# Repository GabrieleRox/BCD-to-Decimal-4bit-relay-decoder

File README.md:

# BCD-to-Decimal 4bit relay decoder

This board was born from my passion for retrocomputers and electronics, as an electromechanical reinterpretation of a modern circuit with the aim of creating a set of simple logic operators schemes. Initially conceived as a component of an electromechanical clock, it can be adapted to any type of application, thanks to a simple design that is easy to adapt to different operating conditions.

The scheme of this board was inspired by the logic scheme of an IC of the 4000 family, converting the logic gates into electromechanical logic. The scheme obtained was then optimized trying to exploit all the available contacts of the relays, in order to create a compact board and as simple as possible and with few connections.

## Features

There are 28 HRS1H-S-DC12V signal relays on the board. These are 12V 6-pin relays, each of which can support up to 1A of current and consume just 200mW. The use of these relays allows to adapt the board to operate at different voltages, by appropriately choosing the operating voltage of the relays. The output is designed for the direct driving of a 7-segment display with common anode, which can be powered in this way even at a voltage different from that of the board. 4 LEDs have also been included to display the input binary code.

Finally, a set of serigraphs guides the user in fixing and connecting.

## Technical specifications

- Power supply voltage: 12V
- Current per channel: max 1.8A
- Current supported for each segment: max 1A
- Board size: 100 x 83.5 mm
- Dimension for fixing: 93 x 75 mm

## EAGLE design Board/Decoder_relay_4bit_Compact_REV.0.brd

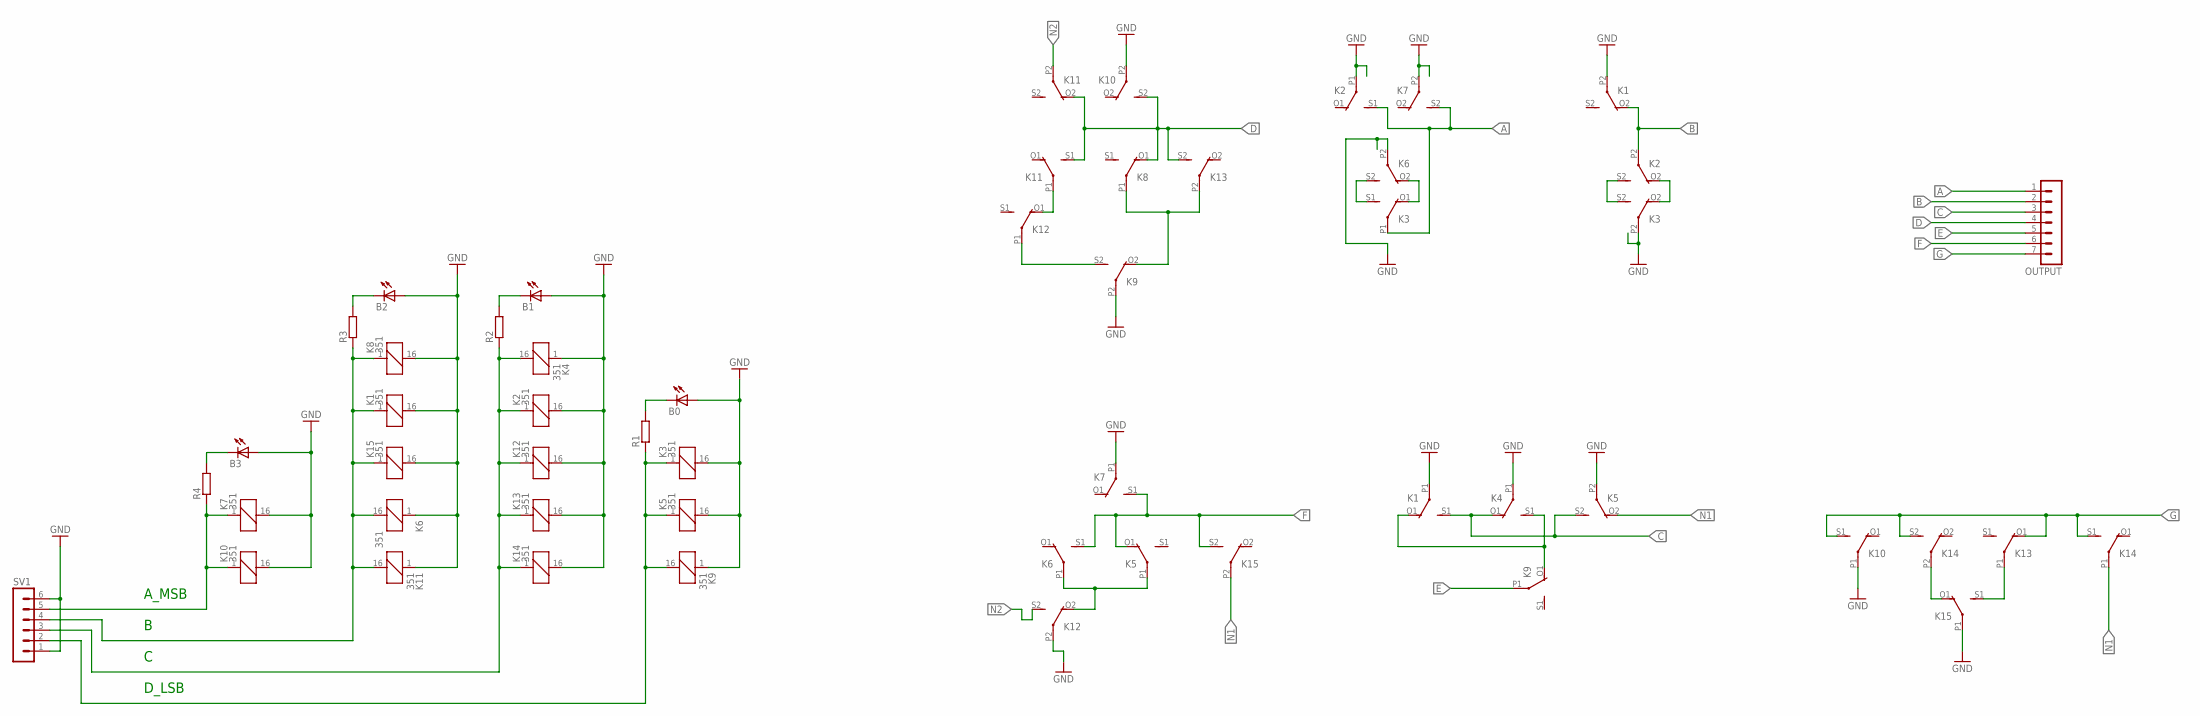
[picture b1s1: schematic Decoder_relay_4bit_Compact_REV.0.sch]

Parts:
B0, B1, B2, B3: LED3MM
K1, K2, K3, K4, K5, K6, K7, K8, K9, K10, K11, K12, K13, K14, K15: 351
OUTPUT: MA07-1
R1, R2, R3, R4: R-EU_M0805; M0805
SV1: MA06-1

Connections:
A: K2.S1 (S), K3.P1, K7.S2 (S), OUTPUT.1
A3: K7.1, K10.1, R4.1, SV1.5
B: K1.O2 (O), K2.P2, OUTPUT.2
C: K1.S1 (S), K4.O1 (O), K5.S2 (S), OUTPUT.3
D: K8.O1 (O), K10.S2 (S), K11.O2 (O), K11.S1 (S), K13.S2 (S), OUTPUT.4
E: K9.P1, OUTPUT.5
F: K5.O1 (O), K6.S1 (S), K7.S1 (S), K15.S2 (S), OUTPUT.6
G: K10.S1 (S), K13.O1 (O), K14.S1 (S), K14.S2 (S), OUTPUT.7
GND: B0.A, B1.A, B2.A, B3.A, K1.16 (2), K1.P1, K1.P2, K2.16 (2), K2.P1, K3.16 (2), K3.P2, K4.1, K4.P1, K5.16 (2), K5.P2, K6.1, K6.P2, K7.16 (2), K7.P1, K7.P2, K8.16 (2), K9.1, K9.P2, K10.16 (2), K10.P1, K10.P2, K11.1, K12.16 (2), K12.P2, K13.16 (2), K14.16 (2), K15.16 (2), K15.P1, SV1.1, SV1.6
N1: K5.O2 (O), K14.P1, K15.P2
N2: K11.P2, K12.S2 (S)
unnamed: K8.P1, K9.O2 (O), K13.P2
unnamed: B0.K (C), R1.2
unnamed: K2.S2 (S), K3.S2 (S)
unnamed: B1.K (C), R2.2
unnamed: K3.S1 (S), K6.S2 (S)
unnamed: B2.K (C), R3.2
unnamed: B3.K (C), R4.2
unnamed: K5.P1, K6.P1, K12.O2 (O)
unnamed: K2.O2 (O), K3.O2 (O)
unnamed: K13.P1, K15.S1 (S)
unnamed: K14.P2, K15.O1 (O)
unnamed: K9.S2 (S), K12.P1
unnamed: K11.P1, K12.O1 (O)
unnamed: K3.O1 (O), K6.O2 (O)
unnamed: K1.O1 (O), K4.S1 (S), K9.O1 (O)
unnamed: K1.1, K6.16 (2), K8.1, K11.16 (2), K15.1, R3.1, SV1.4
unnamed: K3.1, K5.1, K9.16 (2), R1.1, SV1.2
unnamed: K2.1, K4.16 (2), K12.1, K13.1, K14.1, R2.1, SV1.3

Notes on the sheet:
A_MSB
D_LSB

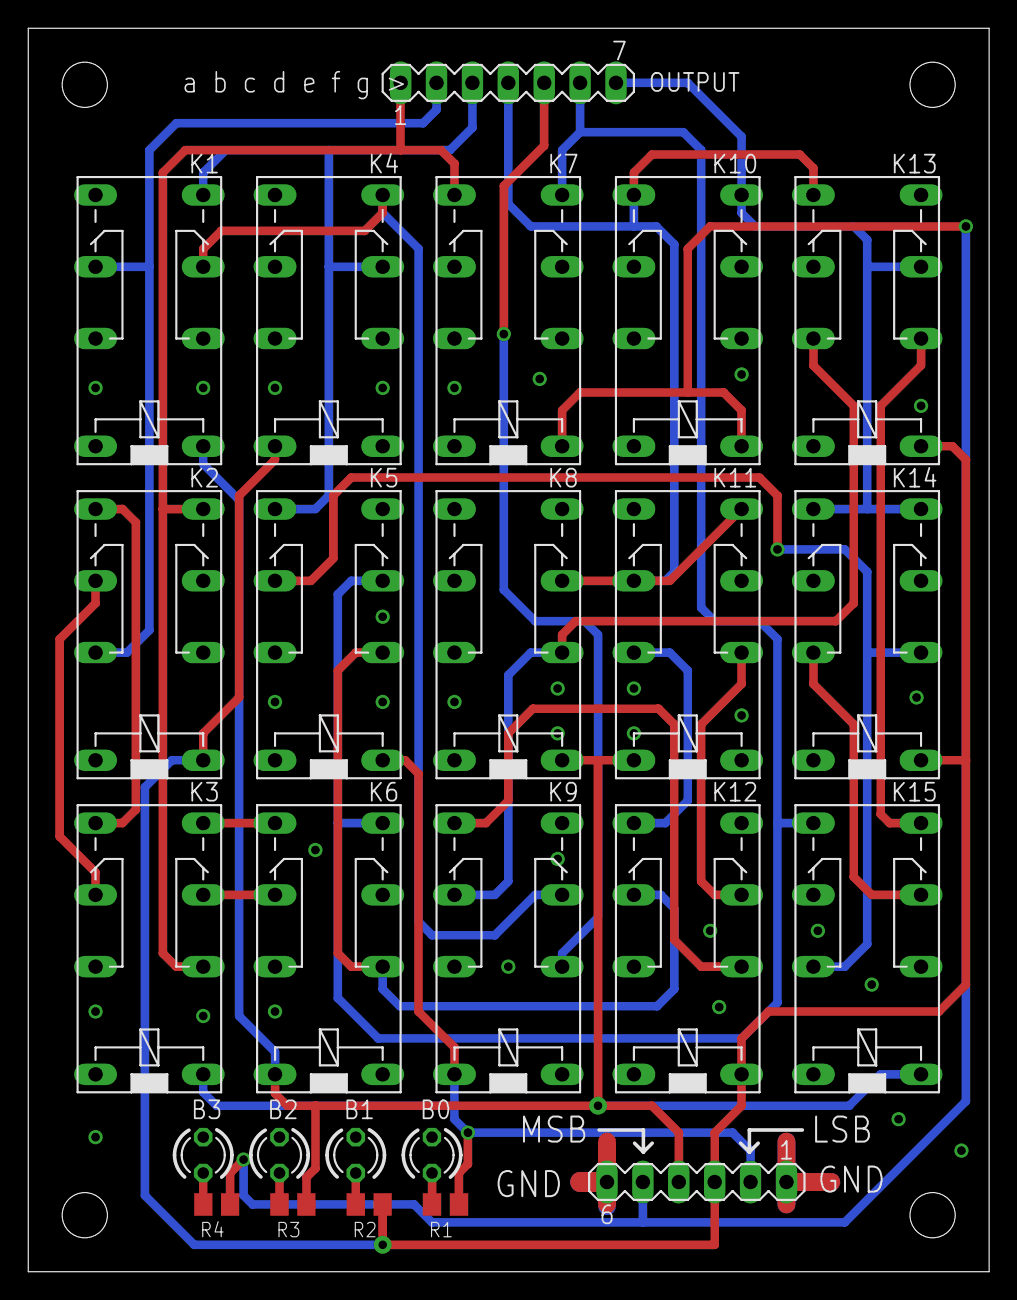
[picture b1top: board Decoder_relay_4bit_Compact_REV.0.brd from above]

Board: 2 copper layers, 68.0 x 88.0 mm, 25 parts (0 on the bottom side), 29 nets.

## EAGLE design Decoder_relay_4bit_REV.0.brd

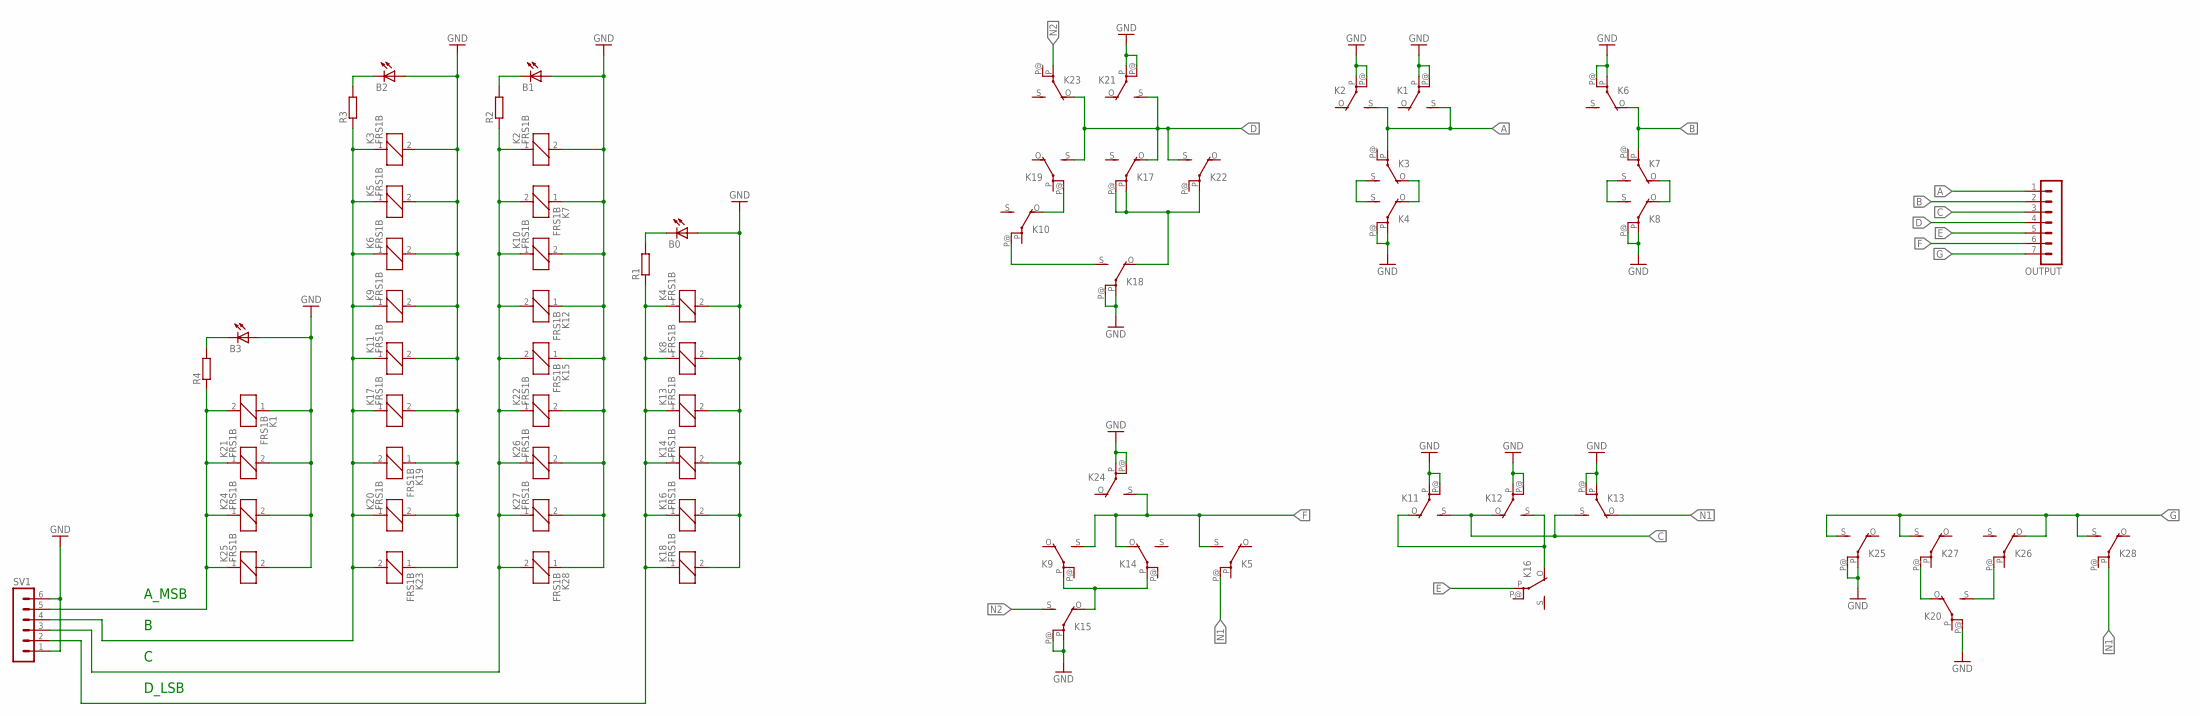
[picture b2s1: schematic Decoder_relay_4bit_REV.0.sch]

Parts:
B0, B1, B2, B3: LED3MM
K1, K2, K3, K4, K5, K6, K7, K8, K9, K10, K11, K12, K13, K14, K15, K16, K17, K18, K19, K20, K21, K22, K23, K24, K25, K26, K27, K28: FRS1B
OUTPUT: MA07-1
R1, R2, R3, R4: R-EU_M1206; M1206
SV1: MA06-1

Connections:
A: K1.S, K2.S, K3.P, OUTPUT.1
A3: K1.2, K21.1, K24.1, K25.1, R4.1, SV1.5
B: K6.O, K7.P, OUTPUT.2
C: K11.S, K12.O, K13.S, OUTPUT.3
D: K17.O, K19.S, K21.S, K22.S, K23.O, OUTPUT.4
E: K16.P, OUTPUT.5
F: K5.S, K9.S, K14.O, K24.S, OUTPUT.6
G: K25.S, K26.O, K27.S, K28.S, OUTPUT.7
GND: B0.A, B1.A, B2.A, B3.A, K1.1, K1.P, K1.P@, K2.2, K2.P, K2.P@, K3.2, K4.2, K4.P, K4.P@, K5.2, K6.2, K6.P, K6.P@, K7.1, K8.2, K8.P, K8.P@, K9.2, K10.2, K11.2, K11.P, K11.P@, K12.1, K12.P, K12.P@, K13.2, K13.P, K13.P@, K14.2, K15.1, K15.P, K15.P@, K16.2, K17.2, K18.2, K18.P, K18.P@, K19.1, K20.2, K20.P@, K21.2, K21.P, K21.P@, K22.2, K23.1, K24.2, K24.P, K24.P@, K25.2, K25.P, K25.P@, K26.2, K27.2, K28.1, SV1.1, SV1.6
N1: K5.P@, K13.O, K28.P
N2: K15.S, K23.P
unnamed: K17.P, K17.P@, K18.O, K22.P
unnamed: B0.K (C), R1.2
unnamed: K7.S, K8.S
unnamed: B1.K (C), R2.2
unnamed: K3.S, K4.S
unnamed: B2.K (C), R3.2
unnamed: B3.K (C), R4.2
unnamed: K9.P, K14.P, K15.O
unnamed: K7.O, K8.O
unnamed: K20.S, K26.P@
unnamed: K20.O, K27.P@
unnamed: K10.P@, K18.S
unnamed: K10.O, K19.P@
unnamed: K3.O, K4.O
unnamed: K11.O, K12.S, K16.O
unnamed: K3.1, K5.1, K6.1, K9.1, K11.1, K17.1, K19.2, K20.1, K23.2, R3.1, SV1.4
unnamed: K4.1, K8.1, K13.1, K14.1, K16.1, K18.1, R1.1, SV1.2
unnamed: K2.1, K7.2, K10.1, K12.2, K15.2, K22.1, K26.1, K27.1, K28.2, R2.1, SV1.3

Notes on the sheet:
A_MSB
D_LSB

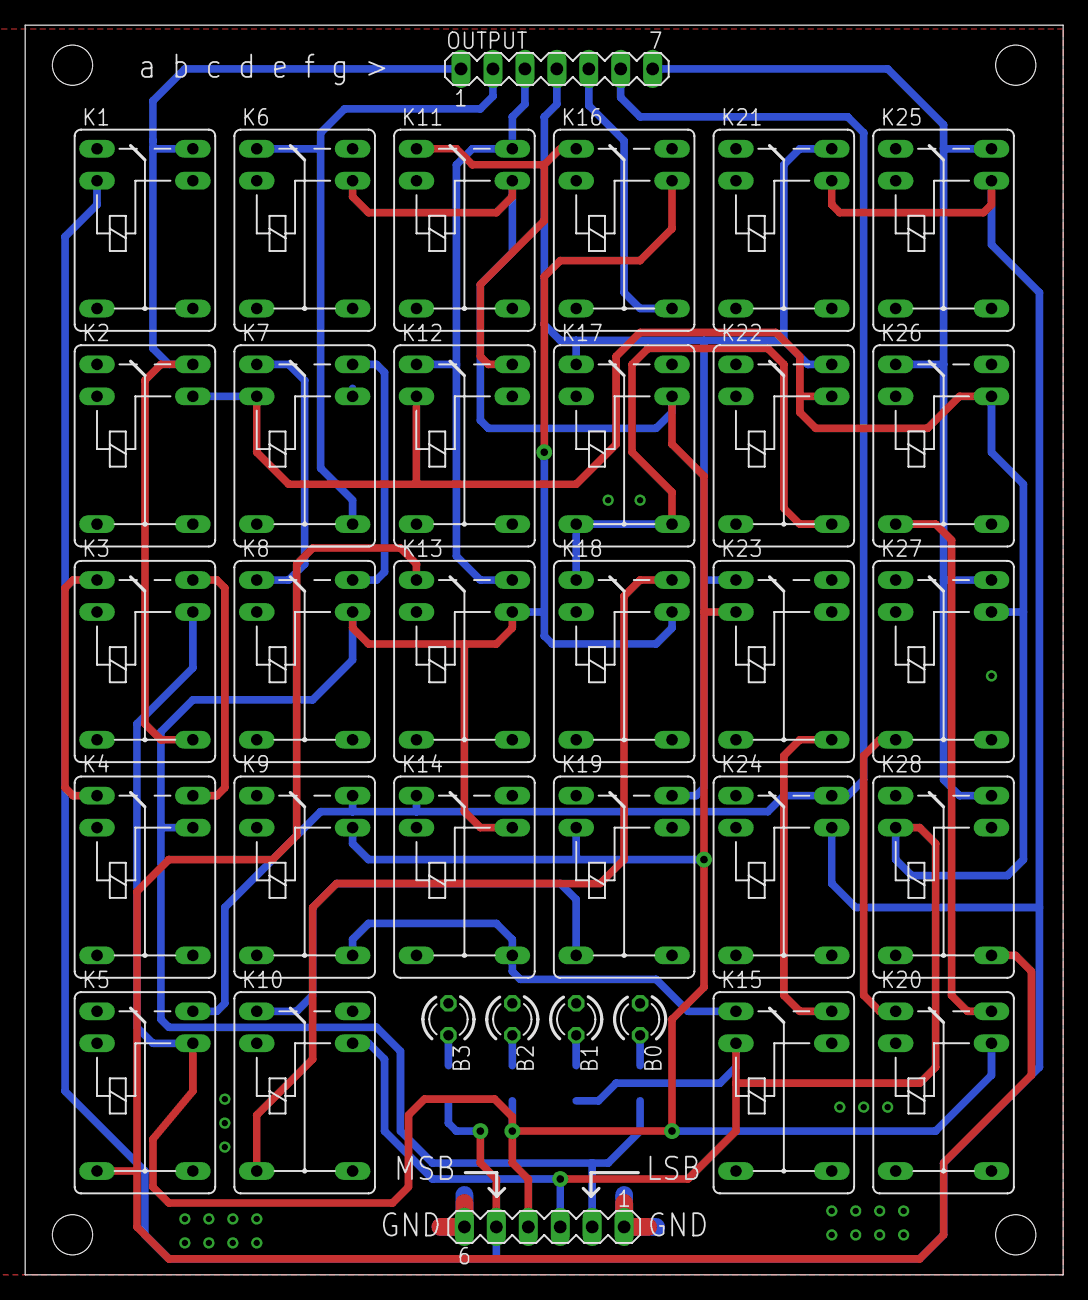
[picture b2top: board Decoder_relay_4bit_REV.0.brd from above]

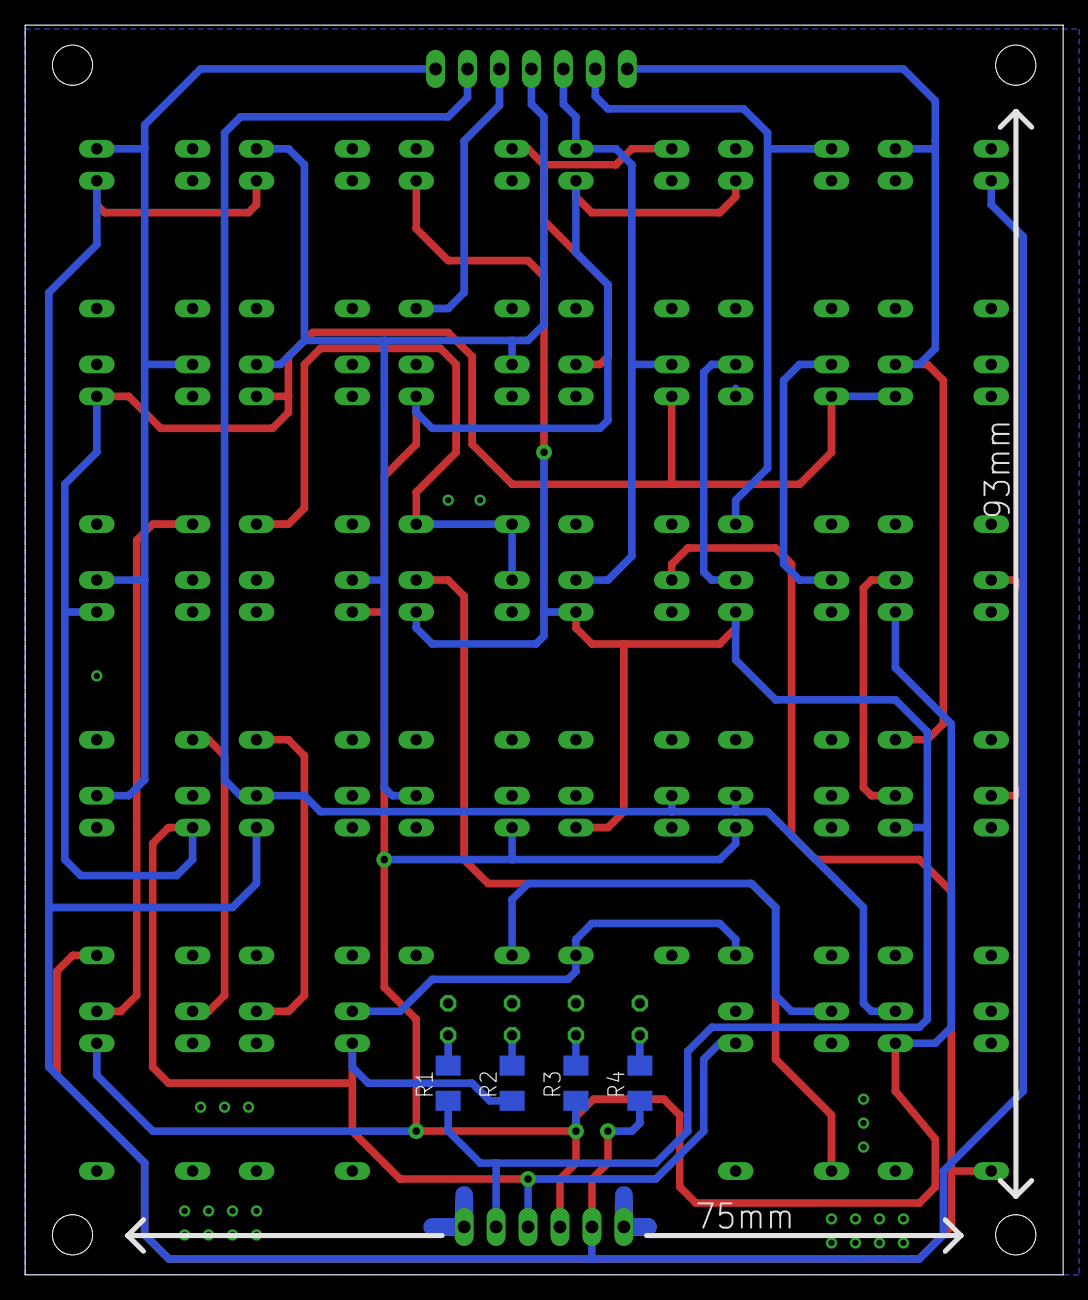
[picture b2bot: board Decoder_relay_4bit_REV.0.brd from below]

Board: 2 copper layers, 82.5 x 99.4 mm, 38 parts (4 on the bottom side), 29 nets.

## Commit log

2022-01-28 First upload
2022-01-28 Eagle file first upload
2022-02-11 Upload compact version
